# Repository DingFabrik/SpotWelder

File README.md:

# SpotWelder
Arduino SW for a Spotwelder, schematic and layout

A project of DingFabrik Köln
https://wiki.dingfabrik.de/index.php/Punktschwei%C3%9Fger%C3%A4t

BOM:
- Arduino Uno (or compatible)
- LCD Keypad Shield
- DIY Solid State Relay with zero point crossing detector (Eagle files)
 
Connections:
- X3-2 Arduino GND
- X4-2 Arduino D3
- X4-1 Arduino D2
- Y3-1 Arduino 5V
- X1-2 230 VAC
- X1-1 230 VAC
- X2-2 Transformer 
- X2-1 Transformer

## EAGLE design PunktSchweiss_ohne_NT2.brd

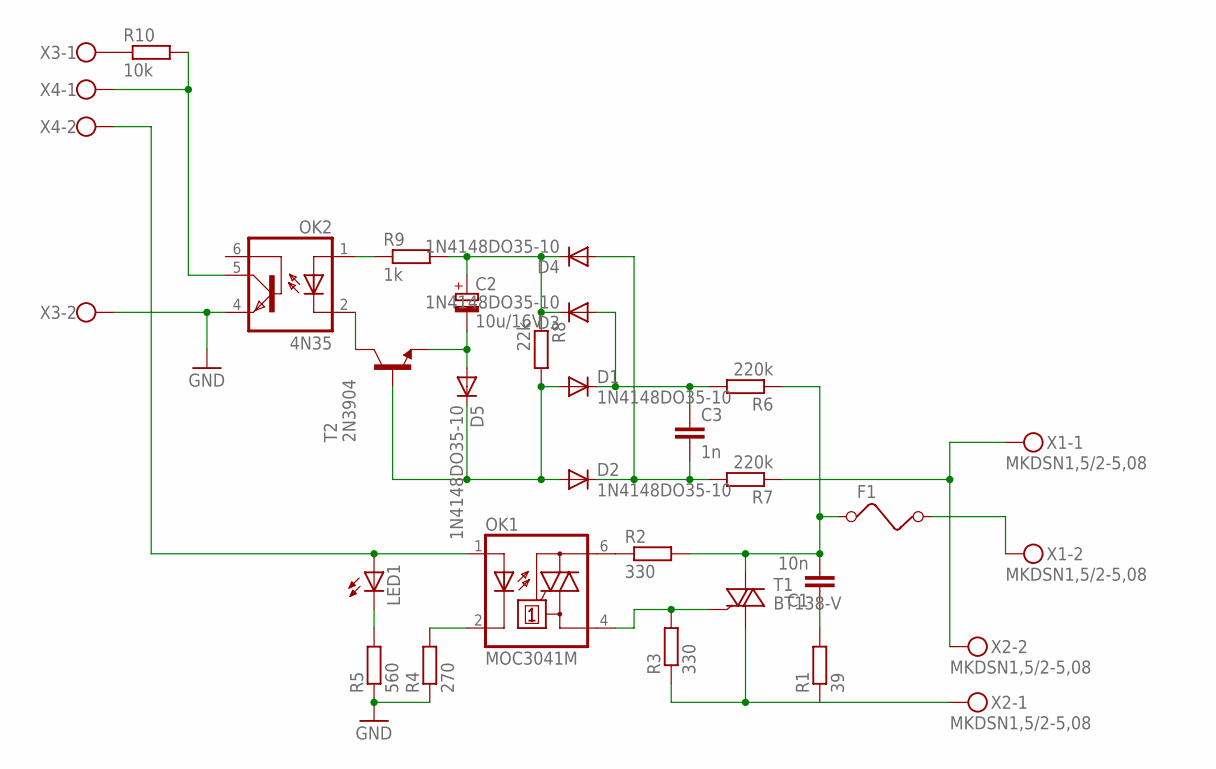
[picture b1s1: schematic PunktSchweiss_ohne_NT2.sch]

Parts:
C1: 10n; C102-043X133
C2: 10u/16V; E1,8-4
C3: 1n; C050-030X075
D1, D2, D3, D4, D5: 1N4148DO35-10; DO35-10
F1: FUSE
LED1: LED3MM
OK1: MOC3041M; DIL06
OK2: 4N35; DIL06
R1: 39; 0207/10
R2, R3: 330; 0207/10
R4: 270; 0207/10
R5: 560; 0207/10
R6, R7: 220k; 0207/10
R8: 22k; 0207/10
R9: 1k; 0207/10
R10: 10k; 0207/10
T1: BT138-V; TO220BV
T2: 2N3904; TO92
X1, X2: MKDSN1,5/2-5,08
X3, X4: W237-102

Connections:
D3: LED1.A, OK1.1 (A), X4.2
GND: OK2.4 (EMI), R4.1, R5.1, X3.2
unnamed: OK1.2 (C), R4.2
unnamed: LED1.K (C), R5.2
unnamed: OK2.5 (COL), R10.2, X4.1
unnamed: R10.1, X3.1
unnamed: C1.2, F1.1, R2.2, R6.1, T1.T2 (A2)
unnamed: OK1.4 (A1), R3.2, T1.G
unnamed: C1.1, R1.2
unnamed: OK1.6 (A2), R2.1
unnamed: C2.+, D3.C, D4.C, R8.1, R9.2
unnamed: R1.1, R3.1, T1.T1 (A1), X2.1
unnamed: R7.1, X1.1, X2.2
unnamed: F1.2, X1.2
unnamed: D1.A, D2.A, D5.C, R8.2, T2.2 (B)
unnamed: C3.1, D1.C, D3.A, R6.2
unnamed: C3.2, D2.C, D4.A, R7.2
unnamed: C2.-, D5.A, T2.3 (E)
unnamed: OK2.1 (A), R9.1
unnamed: OK2.2 (C), T2.1 (C)

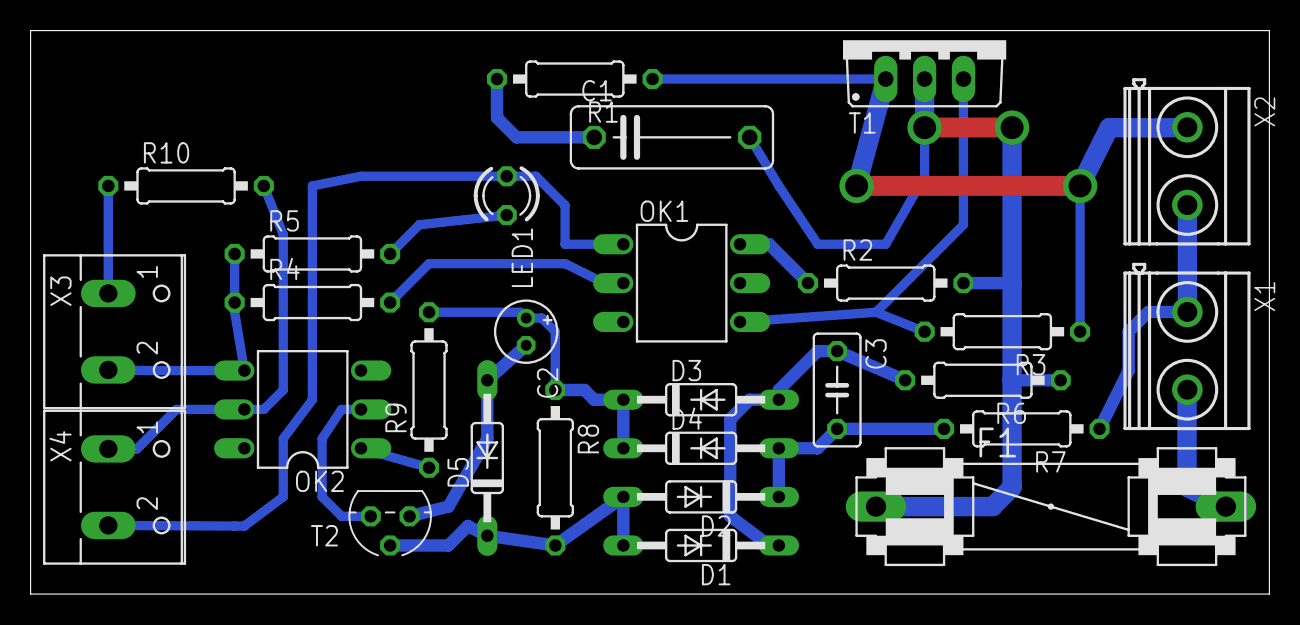
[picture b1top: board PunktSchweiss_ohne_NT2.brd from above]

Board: 2 copper layers, 81.0 x 36.8 mm, 28 parts (0 on the bottom side), 20 nets.
